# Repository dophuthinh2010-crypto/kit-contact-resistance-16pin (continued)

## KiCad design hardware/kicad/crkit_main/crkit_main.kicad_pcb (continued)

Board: 2 copper layers, 161 parts (0 on the bottom side), 175 nets, no tracks yet.

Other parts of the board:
H1, H2, H3, H4: M3; MountingHole_3.2mm_M3

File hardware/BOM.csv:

Group,Ref,Part / function,Model (manufacturer part no.),Qty,Unit price,Line total,Supplier,Alternative part,Price basis,Notes
Device under test,J_JACK (male),"Rack & panel plug, 16 way, PC tail",ITW McMurdo RP16-T,1,20,20,Farnell / element14,"DRP116-T (same plug, DAP body); RPD16 if you need guide dowels",Quoted,Price is for the RP16 solder version ($19.73–21.25). element14 shows RP16 as 'No longer stocked': check availability first.
Device under test,J_JACK (female),"Rack & panel socket, 16 way, PC tail",ITW McMurdo RS16P-T,1,20,20,Farnell / element14,DRS116P-T (DAP body); RSD16 for guide dowels,Estimate,Assumed similar to the plug. RS16 also shows 'No longer stocked' at element14.
Main board,U16,ESP32 development board,Espressif ESP32-DevKitC-32E,1,10,10,DigiKey 1965-ESP32-DEVKITC-32E-ND,ESP32-DevKitC-VE (WROVER); local ESP32 DevKit with CP2102,Quoted,Micro-USB: needs a USB-C to Micro-USB data cable. Power it from USB only.
Main board,U2,"Adjustable regulator used as 0.625 A current source, TO-220",TI LM317T,1,0.45,0.45,LCSC / DigiKey,"ST LM317T, onsemi LM317TG",Estimate,Rev C: I = 1.25 V / R_SET. Fit the clip-on heatsink.
Main board,HS1,"Clip-on TO-220 heatsink, about 20 °C/W",Aavid 577202B00000G,1,0.6,0.6,DigiKey,Any TO-220 clip heatsink 18-25 °C/W,Estimate,About 2.2 W while a pin is on.
Main board,U15,"16-bit ADC, 4 ch, I2C",TI ADS1115IDGSR,1,1.33,1.33,LCSC C37593,ADS1115 breakout module (for a hand-wired prototype),Quoted,LCSC showed 0 stock on one listing; DigiKey ~$3.59.
Main board,U5–U14,"Triple SPDT analog switch, DIP-16 (two 16-to-1 sense trees)",TI CD4053BE,10,0.45,4.5,LCSC / DigiKey,"Nexperia HEF4053BP, CD4053BM96 (SOIC)",Estimate,"Rev C: replaces the two CD74HC4067. Sense lines only, no test current."
Main board,"U3, U4",8-bit shift register,TI SN74HC595DR,2,0.2,0.4,LCSC,Nexperia 74HC595D,Estimate,
Main board,U1,"3.3 V LDO, 600 mA",Diodes AP2112K-3.3TRG1,1,0.1,0.1,LCSC,AMS1117-3.3 (SOT-223),Estimate,Analog 3.3 V rail.
Main board,Q4–Q19,"N-MOSFET, logic level, SOT-23",AOS AO3400A,16,0.03,0.48,LCSC,Vishay Si2302CDS,Estimate,One per contact (pin select).
Main board,"Q1, Q3","P-MOSFET, SOT-23",AOS AO3401A,2,0.03,0.06,LCSC,Vishay Si2301CDS,Estimate,Q3 = test current enable (Q_EN). Q1 = reverse-polarity protection (rev B).
Main board,Q2,N-MOSFET small signal,2N7002,1,0.02,0.02,LCSC,BSS138,Estimate,
Main board,R4 (R_SET),"Metal-oxide resistor 2.0 Ω 1 %, 3 W, axial",Vishay PR03000202008JAC00,1,0.2,0.2,DigiKey,"Any 2.0 Ω 3 W, 1 %",Estimate,Sets the test current; 0.78 W in use. Mount 2 mm off the board.
Main board,R5 (R_SH),"Current shunt 0.1 Ω 1 %, 1 W, 2512",Yageo PE2512FKF070R1L,1,0.12,0.12,LCSC,Vishay WSL2512R1000FEA,Estimate,Read by ADS1115 AIN2-AIN3 with Kelvin taps.
Main board,R (misc),"Thick-film resistors 1 %, 0603: 10 kΩ ×40, 100 kΩ ×17, 100 Ω ×16, 1 kΩ ×5, 4.7 kΩ ×2, 3.3 kΩ",UNI-ROYAL 0603WAF series,81,0.003,0.243,LCSC,Yageo RC0603FR-07 series,Estimate,
Main board,"D3, D4","Dual Schottky clamp, SOT-23",Nexperia BAT54S,2,0.02,0.04,LCSC,BAT54SW (SOT-323),Estimate,ADS1115 contact inputs.
Main board,D2,TVS diode 5 V,Littelfuse SMBJ5.0A,1,0.05,0.05,LCSC,SMAJ5.0A,Estimate,
Main board,F1,"Polyfuse 2 A hold, 1812",Bourns MF-MSMF200-2,1,0.15,0.15,LCSC,Littelfuse 1812L200,Estimate,
Main board,C1,Electrolytic 470 µF 10 V,Panasonic EEU-FR1A471,1,0.15,0.15,LCSC,Any low-ESR 470 µF 16 V,Estimate,
Main board,C (misc),"Ceramic caps: 100 nF ×18 (0603), 10 µF ×2 and 1 µF (0805)",Samsung CL series,21,0.01,0.21,LCSC,Murata GRM series,Estimate,
Main board,D5,LED green 0805,Generic,1,0.02,0.02,LCSC,,Estimate,
Main board,J1,DC barrel jack 5.5/2.1 mm,CUI PJ-002A,1,0.6,0.6,LCSC / DigiKey,Generic DC-005,Estimate,
Main board,"J2, J3","Box header 2×17, 2.54 mm",Amphenol T821134A1S100CEU,2,0.3,0.6,LCSC,Generic 34-pin IDC box header,Estimate,Ribbon to the jack boards.
Main board,J4,JST XH 2-pin header,JST B2B-XH-A,1,0.05,0.05,LCSC,Generic XH 2.54,Estimate,Mate-detect switch.
Main board,J5,"Pin header 1×4, 2.54 mm",Generic 2.54 mm,1,0.03,0.03,LCSC,,Estimate,I2C spare.
Main board,MCU socket,"Female header 1×19, 2.54 mm",Generic,2,0.15,0.3,LCSC,,Estimate,Lets the ESP32 board plug in.
Main board,D1,"Zener 5.1 V, SOD-123",Diodes BZT52C5V1,1,0.02,0.02,LCSC,MMSZ5231B,Estimate,Rev B: Q1 gate clamp.
Jack boards,J_IDC,"Box header 2×17, 2.54 mm",Amphenol T821134A1S100CEU,2,0.3,0.6,LCSC,Generic 34-pin IDC box header,Estimate,One per jack board.
Jack boards,Standoffs,"M3 brass standoff, 7 mm (plug) and 8 mm (socket)",Generic M3,4,0.1,0.4,LCSC / local,,Estimate,Plates sit 7.1 / 7.9 mm above the board: shim with a washer.
Cables & power,"W1, W2","34-way IDC ribbon, 30 cm, with 2 IDC sockets",3M 3365/34 + 3M 89134 sockets,2,1.5,3.0,LCSC / DigiKey,Generic 34P ribbon assembly,Estimate,
Cables & power,PSU,"5 V 2 A adapter, 5.5/2.1 mm plug",Mean Well GST18A05-P1J,1,8,8,DigiKey / Mouser,Generic 5 V 2 A adapter (~$3),Estimate,
Cables & power,USB,"USB-C to Micro-USB data cable, 1 m",Generic,1,2,2,Local,,Estimate,"Must carry data, not charge-only."
PCBs,PCB-1,"Main board 135×101 mm, 2-layer, 2 oz (lot of 5)",JLCPCB,1,22,22,JLCPCB,PCBWay,Estimate,Shipping not included.
PCBs,"PCB-2, PCB-3","Jack boards 80×40 mm, 2-layer, 1 oz (lot of 5 each)",JLCPCB,2,2,4,JLCPCB,PCBWay,Estimate,Two designs (plug and socket footprints).
Fixture,RAIL,"Linear rail MGN12H, 150 mm, with carriage",HIWIN MGN12H,1,15,15,AliExpress / local,Genuine HIWIN (~$60),Estimate,Price for a generic rail.
Fixture,MECH,"Base plate, female-board bracket, carriage clamp (aluminium)",Custom machined,1,30,30,Local machine shop,3D-printed brackets on an aluminium plate,Estimate,
Fixture,SW,"Mate-detect microswitch, lever",Omron D2F-01L,1,1.5,1.5,DigiKey / LCSC,KW11-3Z generic,Estimate,
Fixture,HW,"Handle knob, M3/M4 screws, rubber feet",Generic,1,5,5,Local,,Estimate,
Calibration,SHUNT,"Reference shunt 10 mΩ, 4-terminal (Kelvin), 1 %",Vishay WSK2512R0100FEA,1,2,2,DigiKey / Mouser,Bourns CSS2H-2512K-10L0F,Estimate,For 'Calibrate with shunt'.
Calibration,SHORT,"Shorting bar (copper), force and sense shorted",Made in-house,1,2,2,Local,,Estimate,For 'Calibrate zero'.
TOTAL per kit (USD),,,,,,156.22,,,,"Unit price at qty 1, USD, excl. tax and shipping. 'Quoted' = distributor price seen 18 Nov 2026; 'Estimate' = typical price, check before ordering."

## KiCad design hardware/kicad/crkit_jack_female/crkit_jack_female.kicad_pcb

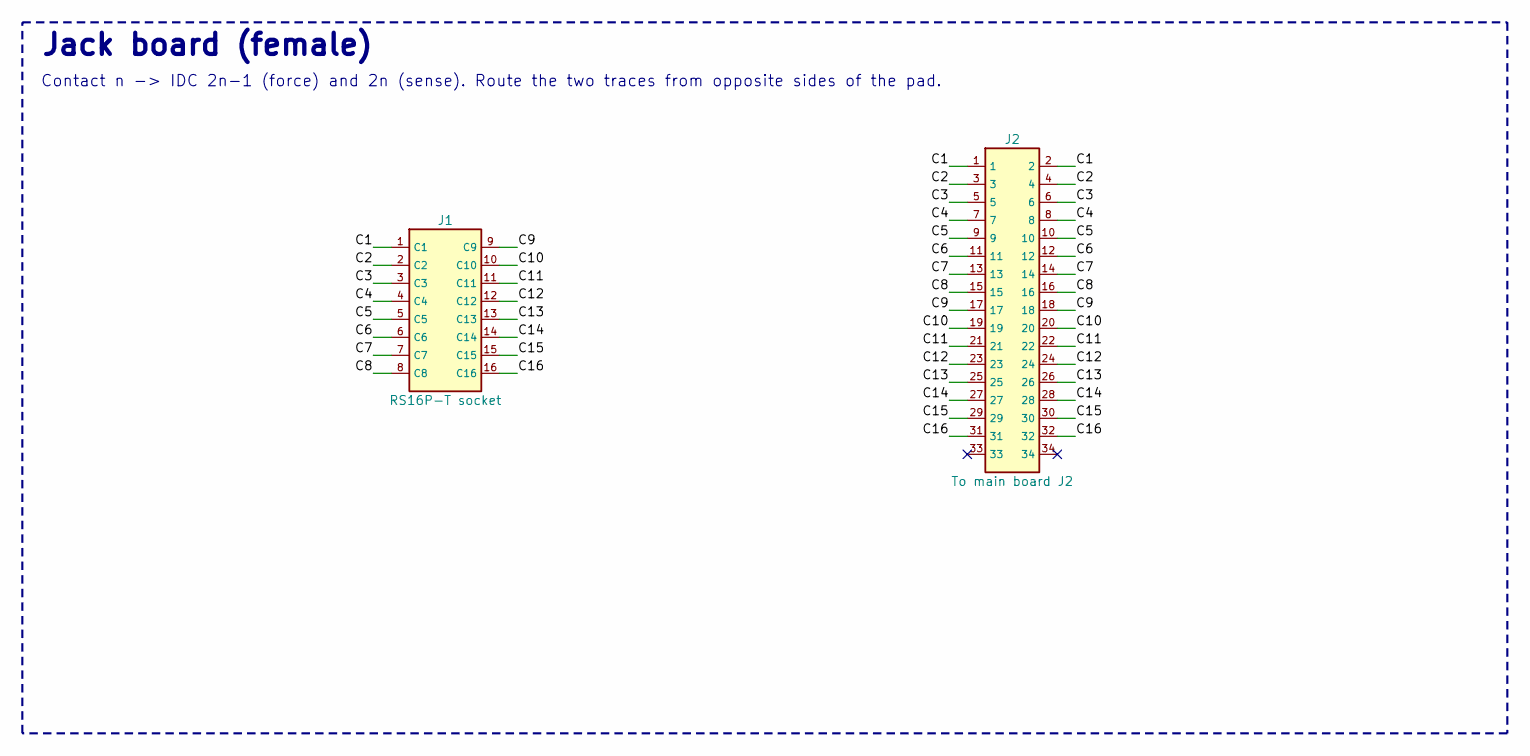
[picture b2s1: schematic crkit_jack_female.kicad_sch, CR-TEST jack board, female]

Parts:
J1: RS16P-T socket; McMurdo_RedRange_Socket_16way_RS16P-T; MPN ITW McMurdo RS16P-T
J2: To main board J2; IDC-Header_2x17_P2.54mm_Vertical; MPN Amphenol T821134A1S100CEU

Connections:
C1: J1.1 (C1), J2.1, J2.2
C2: J1.2 (C2), J2.3, J2.4
C3: J1.3 (C3), J2.5, J2.6
C4: J1.4 (C4), J2.7, J2.8
C5: J1.5 (C5), J2.9, J2.10
C6: J1.6 (C6), J2.11, J2.12
C7: J1.7 (C7), J2.13, J2.14
C8: J1.8 (C8), J2.15, J2.16
C9: J1.9 (C9), J2.17, J2.18
C10: J1.10 (C10), J2.19, J2.20
C11: J1.11 (C11), J2.21, J2.22
C12: J1.12 (C12), J2.23, J2.24
C13: J1.13 (C13), J2.25, J2.26
C14: J1.14 (C14), J2.27, J2.28
C15: J1.15 (C15), J2.29, J2.30
C16: J1.16 (C16), J2.31, J2.32

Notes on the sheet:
Jack board (female)
Contact n -> IDC 2n-1 (force) and 2n (sense). Route the two traces from opposite sides of the pad.

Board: 2 copper layers, 6 parts (0 on the bottom side), 16 nets, no tracks yet.

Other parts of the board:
H1, H2, H3, H4: M3; MountingHole_3.2mm_M3

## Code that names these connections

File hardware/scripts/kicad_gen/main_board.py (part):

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C("10u", "LM_IN", "GND", (31.5, 5, 0), B, mpn="Samsung CL21 X5R", fp=F_0805)
C("100n", "LM_IN", "GND", (36, 5, 0), B)
add("U", "LM317T", S_LM317, F_TO220, {"3": "LM_IN", "2": "LM_OUT", "1": "F_BUS"}, (32, 12, 0), B, "TI LM317T (TO-220) + clip-on heatsink",
    "Rev C: constant-current source. I = 1.25 V / 2.0 ohm = 0.625 A into F_BUS, whatever the contact. Needs about 3.5 V of the 5 V.")
add("R", "2.0R 3W 1%", S_R, F_R3W, {"1": "LM_OUT", "2": "F_BUS"}, (44, 12, 0), B, "Vishay PR03000202008JAC00 (or any 2.0 ohm 3 W)",
    "R_SET: sets the test current. 0.78 W in normal use")
add("R", "0.1R 1% 2512", S_R, F_2512, {"1": "LO_RTN", "2": "GND"}, (64, 20, 0), B, "Yageo PE2512FKF070R1L",
    "R_SH: current shunt, read by ADS1115 AIN2-AIN3 (Kelvin taps)")
add("TP", "LO_RTN", S_TP, F_TP, {"1": "LO_RTN"}, (55, 20, 0), B)

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
# ----------------------------------------------------------------------------- 7 MCU and I/O
B = "7 ESP32 and I/O"
gpio = {"IO23": "SR_DATA", "IO18": "SR_CLK", "IO5": "SR_LATCH", "IO19": "SR_OE", "IO25": "MUX_S0", "IO26": "MUX_S1", "IO27": "MUX_S2",
        "IO14": "MUX_S3", "IO13": "MUX_EN", "IO32": "I_EN", "IO21": "SDA", "IO22": "SCL", "IO4": "ADC_RDY", "IO33": "MATE_DET",
        "IO17": "LED_IO", "IO34": "V5_MON", "GND": "GND"}
dk = {}
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
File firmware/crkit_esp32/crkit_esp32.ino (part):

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  ITW McMurdo RP16-T / RS16P-T connector and streams the results over USB serial.

  Rev C measurement chain:
    LM317T + 2.0 ohm R_SET  -> constant 0.625 A into F_BUS (female side of every contact)
    Qn (AO3400A) on         -> current returns through contact n and the 0.1 ohm shunt R_SH
    2x CD4053B mux trees    -> select the Kelvin taps either side of contact n
    ADS1115 AIN0-AIN1       -> contact voltage, differential, PGA +-0.256 V (7.8 uV per step)
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#define FW_VERSION "0.5.0"

// ---------------- pin map (docs/design.md) ----------------
const int PIN_SR_DATA  = 23;   // 74HC595 SER
const int PIN_SR_CLK   = 18;   // 74HC595 SRCLK
const int PIN_SR_LATCH = 5;    // 74HC595 RCLK
const int PIN_SR_OE    = 19;   // 74HC595 /OE  (pull-up on board, LOW = outputs on)
const int PIN_MUX_S[4] = {25, 26, 27, 14};   // CD4053B tree levels 1-4: channel n = binary n-1
const int PIN_MUX_EN   = 13;   // CD4053B INH, all ten chips (pull-up on board, LOW = enabled)
const int PIN_I_EN     = 32;   // HIGH = test current on (Q_EN feeds the LM317T)
const int PIN_ADC_RDY  = 4;    // ADS1115 ALERT/RDY (not used, polled over I2C)
const int PIN_MATE     = 33;   // mate-detect switch to GND, LOW = mated
const int PIN_LED      = 17;
const int PIN_V5_MON   = 34;   // 5 V rail through a 10k/10k divider (input-only ADC1 pin)

// ---------------- measurement constants ----------------
const int   NPINS          = 16;
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
// ---------------- low-level helpers ----------------
void shiftPins(uint16_t bits) {             // bit n-1 = MOSFET Qn
  digitalWrite(PIN_SR_LATCH, LOW);
  shiftOut(PIN_SR_DATA, PIN_SR_CLK, MSBFIRST, (bits >> 8) & 0xFF);   // goes on to U4 (contacts 9-16)
  shiftOut(PIN_SR_DATA, PIN_SR_CLK, MSBFIRST, bits & 0xFF);          // stays in U3 (contacts 1-8)
  digitalWrite(PIN_SR_LATCH, HIGH);
}

void allOff() {
  digitalWrite(PIN_I_EN, LOW);
  shiftPins(0);
}

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float avgContact(int n) { float s = 0; for (int i = 0; i < n; i++) s += vContact(); return s / n; }
float avgShunt(int n)   { float s = 0; for (int i = 0; i < n; i++) s += vShunt();   return s / n; }

float readV5() { return analogReadMilliVolts(PIN_V5_MON) * 2.0f / 1000.0f; }

void loadSettings() {
  prefs.begin("crkit", true);
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  float vOff = avgContact(SAMPLES_OFF);        // no current: ADS offset + thermal EMF of this channel
  shiftPins(1u << p);
  delay(1);
  digitalWrite(PIN_I_EN, HIGH);                // current pulse starts (about 40 ms)
  delay(SETTLE_MS);
  float iNow = (vShunt() - vShZero) / R_SHUNT;
  if (iNow > I_OVER_LIMIT) {                   // the LM317T can't give this: switch off at once
    digitalWrite(PIN_I_EN, LOW);
    shiftPins(0);
    rd.i = iNow; rd.vmv = NAN; rd.rraw = NAN; rd.r = NAN; rd.rmin = NAN; rd.flag = "OPEN";
    Serial.printf("ALARM,%ld,OVERCURRENT,%.3f A on pin %d: test current switched off, scan stopped. Check the LM317T and R_SET.\n", cycleCount, iNow, p + 1);
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    float is = vss / R_SHUNT;                  // this sample's own R, to find the lowest of the 8
    if (is > I_OPEN_LIMIT) { float rs = vcs / is * 1000.0f; if (rs < rminRaw) rminRaw = rs; }
  }
  digitalWrite(PIN_I_EN, LOW);                 // current pulse ends
  shiftPins(0);
  vc /= SAMPLES_PIN; vs /= SAMPLES_PIN;

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  // Baseline: every channel's reading with the current off (ADS offset and thermal EMF).
  float base[NPINS];
  shiftPins(0);
  digitalWrite(PIN_I_EN, LOW);
  for (int b = 0; b < NPINS; b++) {
    selectMux(b);
    delayMicroseconds(MUX_SETTLE_US);
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  for (int a = 0; a < NPINS && !alarmed; a++) {
    shiftPins(1u << a);
    delay(1);
    digitalWrite(PIN_I_EN, HIGH);
    delay(SETTLE_MS);
    float ia = (vShunt() - vShZero) / R_SHUNT;
    if (ia > I_OVER_LIMIT) {
      digitalWrite(PIN_I_EN, LOW); shiftPins(0);
      Serial.printf("ALARM,%ld,OVERCURRENT,%.3f A driving pin %d in the isolation test: current switched off.\n", cycleCount, ia, a + 1);
      alarmed = true; break;
    }
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        }
      }
    }
    digitalWrite(PIN_I_EN, LOW);
    shiftPins(0);
  }
  Serial.printf("ISO,%ld,%d\n", cycleCount, found);
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  unsigned long t0 = millis();
  if (countIt) { cycleCount++; saveLong("cycle", cycleCount); }
  digitalWrite(PIN_LED, HIGH);
  digitalWrite(PIN_MUX_EN, LOW);
  allOff();
  delay(2);
  vShZero = avgShunt(8);                       // shunt offset, no current flowing
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  }
  if (isoEnabled && onlyPin < 0 && !alarmed) isolationTest();
  allOff();
  digitalWrite(PIN_MUX_EN, HIGH);
  digitalWrite(PIN_LED, LOW);
  Serial.printf("END,%ld,%lu\n", cycleCount, millis() - t0);
}
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
// ---------------- setup / loop ----------------
void setup() {
  pinMode(PIN_I_EN, OUTPUT);     digitalWrite(PIN_I_EN, LOW);     // current off first
  pinMode(PIN_SR_OE, OUTPUT);    digitalWrite(PIN_SR_OE, HIGH);   // outputs off while clearing
  pinMode(PIN_SR_DATA, OUTPUT);  pinMode(PIN_SR_CLK, OUTPUT);  pinMode(PIN_SR_LATCH, OUTPUT);
  shiftPins(0);
  digitalWrite(PIN_SR_OE, LOW);                                    // now safe to enable
  for (int b = 0; b < 4; b++) pinMode(PIN_MUX_S[b], OUTPUT);
  pinMode(PIN_MUX_EN, OUTPUT);   digitalWrite(PIN_MUX_EN, HIGH);
  pinMode(PIN_MATE, INPUT_PULLUP);
  pinMode(PIN_ADC_RDY, INPUT);
  pinMode(PIN_LED, OUTPUT);      digitalWrite(PIN_LED, LOW);

  Serial.begin(115200);
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  }
  ads.setGain(GAIN_SIXTEEN);                 // +/-0.256 V, 7.8125 uV per bit
  ads.setDataRate(RATE_ADS1115_475SPS);      // ~2 ms per reading, about 2.5 s per scan with the isolation test
  analogSetPinAttenuation(PIN_V5_MON, ADC_11db);
  Serial.println("# CR-TEST kit ready. Send STATUS, SCAN or MEASURE.");
  sayHello();
}
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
